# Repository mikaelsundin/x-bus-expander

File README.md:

# x-bus-expander
Emulated Model Train digital interface for getting upto 64-inputs and 64-outputs.

Setup the interface
======
* Solder everything.
* Connect up to four boards in a chain.
* Modify dip switches so every board have a unique combination.
* Connect USB-cable to PC and install CH340G driver.

How to connect Inputs
======
Switches can be connected to IN1 or IN2, pull-up is located on-board. 
The input signals must be electrical isolated from the rest of the system to not dammage anything.
If other devices that switches will be connected a optocoupler is suggested to electrical isolate the input.
C1-C8, C10-C17 is to avoid interface from inputs.

How to connect Outputs
======
Led:s / lamps can be connected to OUT1 and OUT2. The output voltage is equal to the VIN voltage.
With 2N7002 the maximum load current is 115mA and suggested voltage shall be 24V DC or less on VIN.
Remember to use correct polarity on VIN, marked with + and - on PCB.

How to use the interface
======
If you are running Freiwald TrainController (www.freiwald.com)
 choose "Lenz Digital Plus / LI100(F)" and correct com-port.
 The outputs will be named with Address 1-64
 The inputs will be named with Address 1-8 and Input 1-8

Hardware modification to Arduino nano:
======
UART signal CTS is attached to D9 (easiest done to clones with CH340G USB chip).
A jumper with 120R resistor to disable auto-reset feature is also added.

Hardware
======
The hardware is adapted to fit a single 10x5cm board.
Suggested manufacture is iteadstudio.com or elecrow.com
The PCB must be separated into two parts after manufacture.
Use a hacksaw for example if PCB tickness is 1.6mm. 
If running at 1.2mm the PCB can acually be cut by a ordinary scissors (the scissors will loose sharpness).

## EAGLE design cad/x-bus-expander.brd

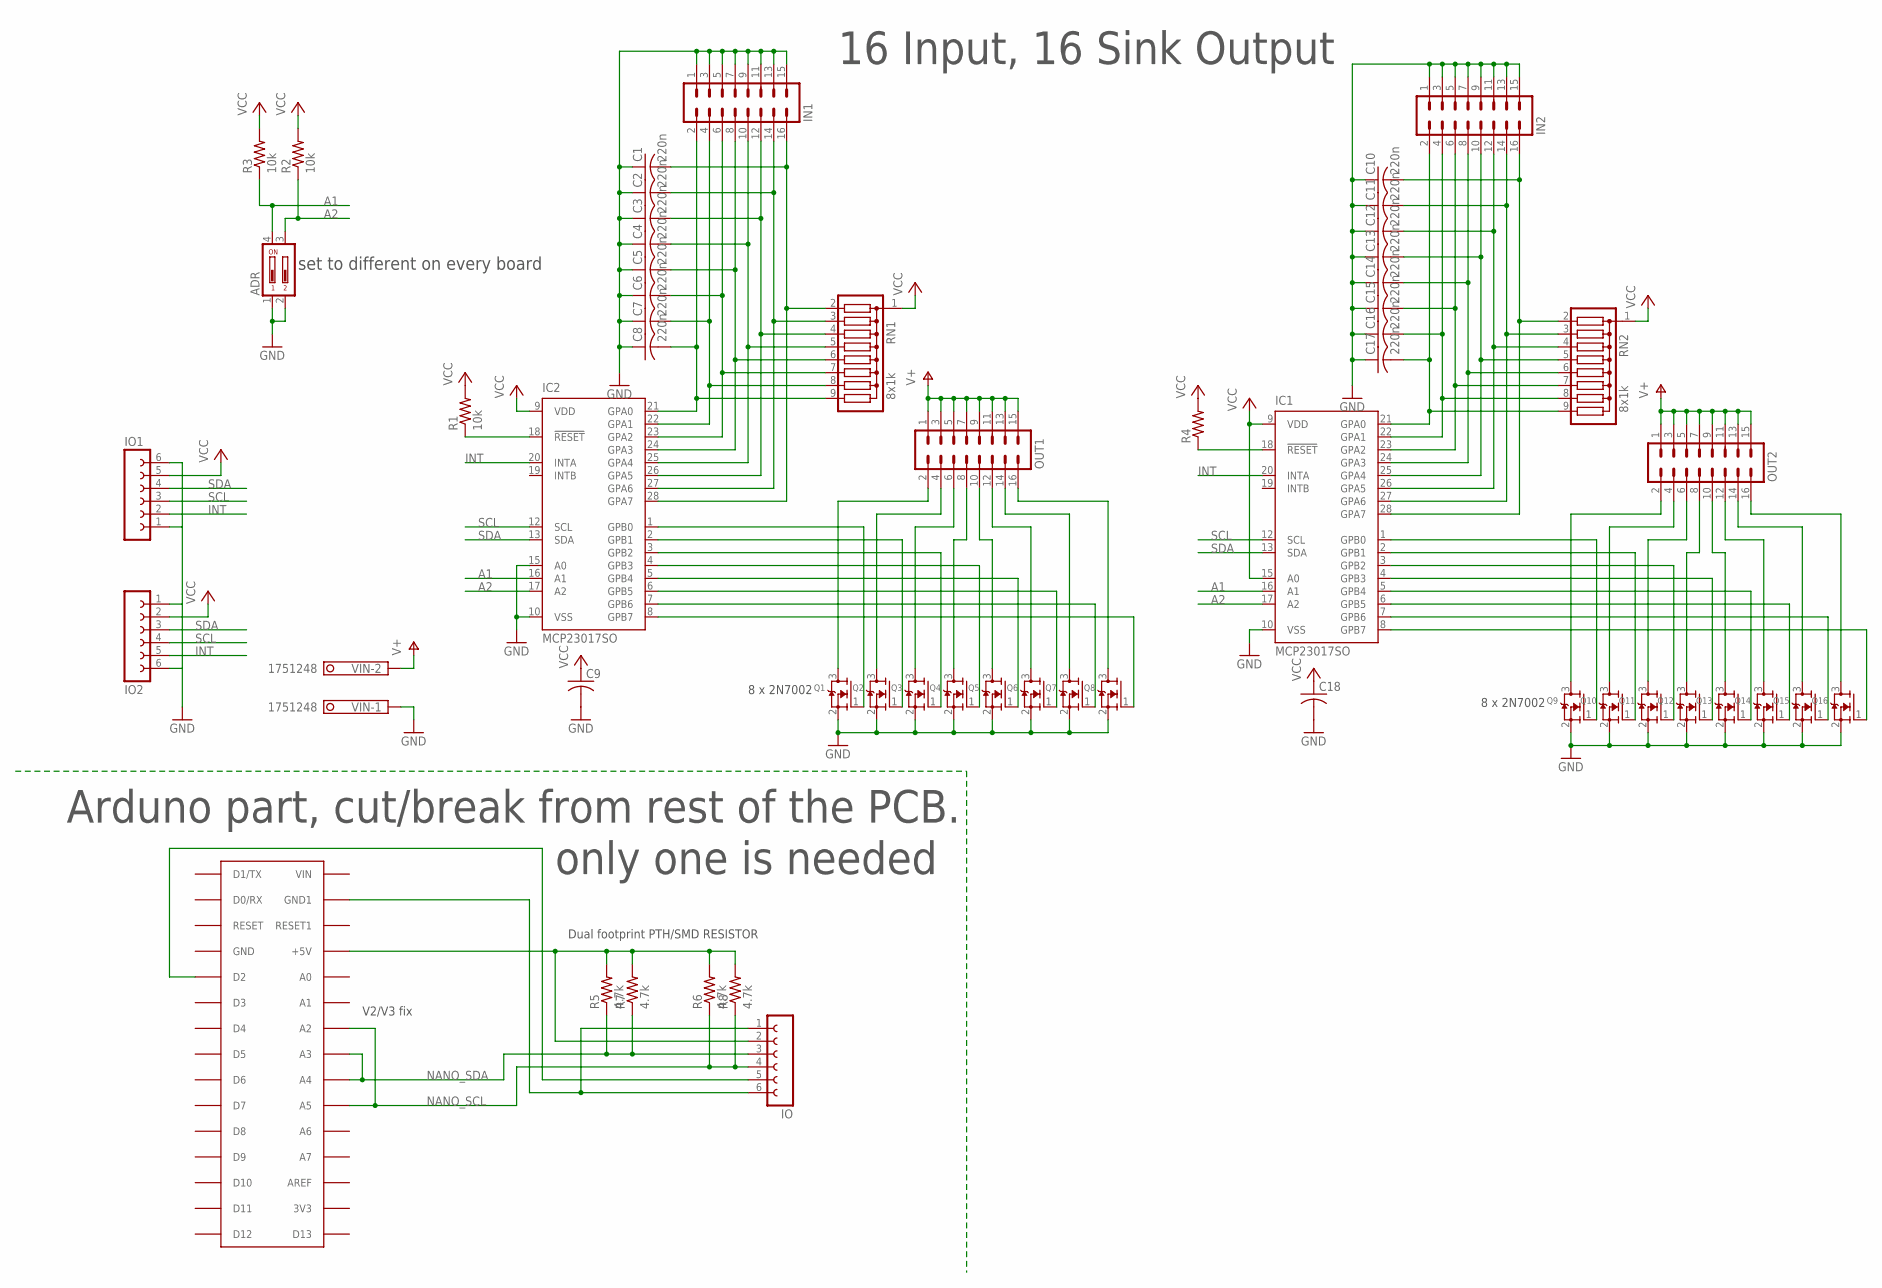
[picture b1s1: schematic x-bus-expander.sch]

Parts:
ADR: DIP02YL
C1, C2, C3, C4, C5, C6, C7, C8, C10, C11, C12, C13, C14, C15, C16, C17: 220n; C0805
C9, C18: C-USC0805; C0805
IC1, IC2: MCP23017SO; SO28W
IN1, IN2: ML16
IO, IO1, IO2: FE06W
OUT1, OUT2: ML16
Q1, Q2, Q3, Q4, Q5, Q6, Q7, Q8, Q9, Q10, Q11, Q12, Q13, Q14, Q15, Q16: MOSFET-NREFLOW; SOT23
R1, R2, R3: 10k; R0603
R4: R-US_R0603; R0603
R5, R6: 4.7k; 0309/10
R7, R8: 4.7k; R0603
RN1, RN2: 8x1k; SIL9
U$1: ARDUINONANO; PDIP-32
VIN: 1751248

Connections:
A1: ADR.4, IC1.16 (A1), IC2.16 (A1), R3.1
A2: ADR.3, IC1.17 (A2), IC2.17 (A2), R2.1
GND: ADR.1, ADR.2, C1.1, C2.1, C3.1, C4.1, C5.1, C6.1, C7.1, C8.1, C9.2, C10.1, C11.1, C12.1, C13.1, C14.1, C15.1, C16.1, C17.1, C18.2, IC1.10 (VSS), IC2.10 (VSS), IC2.15 (A0), IN1.1, IN1.3, IN1.5, IN1.7, IN1.9, IN1.11, IN1.13, IN1.15, IN2.1, IN2.3, IN2.5, IN2.7, IN2.9, IN2.11, IN2.13, IN2.15, IO1.1, IO1.6, IO2.1, IO2.6, Q1.2 (S), Q2.2 (S), Q3.2 (S), Q4.2 (S), Q5.2 (S), Q6.2 (S), Q7.2 (S), Q8.2 (S), Q9.2 (S), Q10.2 (S), Q11.2 (S), Q12.2 (S), Q13.2 (S), Q14.2 (S), Q15.2 (S), Q16.2 (S), VIN.1
INT: IC1.20 (INTA), IC2.20 (INTA), IO1.2, IO2.5
unnamed: OUT1.2, Q1.3 (D)
unnamed: OUT1.4, Q2.3 (D)
unnamed: OUT1.6, Q3.3 (D)
unnamed: OUT1.8, Q4.3 (D)
unnamed: OUT1.10, Q5.3 (D)
unnamed: OUT1.12, Q6.3 (D)
unnamed: OUT1.14, Q7.3 (D)
unnamed: OUT1.16, Q8.3 (D)
unnamed: IC2.1 (GPB0), Q1.1 (G)
unnamed: IC2.2 (GPB1), Q2.1 (G)
unnamed: IC2.3 (GPB2), Q3.1 (G)
unnamed: IC2.4 (GPB3), Q4.1 (G)
unnamed: IC2.5 (GPB4), Q5.1 (G)
unnamed: IC2.6 (GPB5), Q6.1 (G)
unnamed: IC2.7 (GPB6), Q7.1 (G)
unnamed: IC2.8 (GPB7), Q8.1 (G)
unnamed: C8.2, IC2.21 (GPA0), IN1.2, RN1.9
unnamed: C7.2, IC2.22 (GPA1), IN1.4, RN1.8
unnamed: C6.2, IC2.23 (GPA2), IN1.6, RN1.7
unnamed: C5.2, IC2.24 (GPA3), IN1.8, RN1.6
unnamed: C4.2, IC2.25 (GPA4), IN1.10, RN1.5
unnamed: C3.2, IC2.26 (GPA5), IN1.12, RN1.4
unnamed: C2.2, IC2.27 (GPA6), IN1.14, RN1.3
unnamed: C1.2, IC2.28 (GPA7), IN1.16, RN1.2
unnamed: IC2.18 (!RESET), R1.1
unnamed: OUT2.2, Q9.3 (D)
unnamed: OUT2.4, Q10.3 (D)
unnamed: OUT2.6, Q11.3 (D)
unnamed: OUT2.8, Q12.3 (D)
unnamed: OUT2.10, Q13.3 (D)
unnamed: OUT2.12, Q14.3 (D)
unnamed: OUT2.14, Q15.3 (D)
unnamed: OUT2.16, Q16.3 (D)
unnamed: IC1.1 (GPB0), Q9.1 (G)
unnamed: IC1.2 (GPB1), Q10.1 (G)
unnamed: IC1.3 (GPB2), Q11.1 (G)
unnamed: IC1.4 (GPB3), Q12.1 (G)
unnamed: IC1.5 (GPB4), Q13.1 (G)
unnamed: IC1.6 (GPB5), Q14.1 (G)
unnamed: IC1.7 (GPB6), Q15.1 (G)
unnamed: IC1.8 (GPB7), Q16.1 (G)
unnamed: C17.2, IC1.21 (GPA0), IN2.2, RN2.9
unnamed: C16.2, IC1.22 (GPA1), IN2.4, RN2.8
unnamed: C15.2, IC1.23 (GPA2), IN2.6, RN2.7
unnamed: C14.2, IC1.24 (GPA3), IN2.8, RN2.6
unnamed: C13.2, IC1.25 (GPA4), IN2.10, RN2.5
unnamed: C12.2, IC1.26 (GPA5), IN2.12, RN2.4
unnamed: C11.2, IC1.27 (GPA6), IN2.14, RN2.3
unnamed: C10.2, IC1.28 (GPA7), IN2.16, RN2.2
unnamed: IC1.18 (!RESET), R4.1
unnamed: IO.5, U$1.D2
unnamed: IO.1, IO.6, U$1.GND1
unnamed: IO.2, R5.2, R6.2, R7.2, R8.2, U$1.+5V
NANO_SCL: IO.4, R6.1, R8.1, U$1.A2, U$1.A5
NANO_SDA: IO.3, R5.1, R7.1, U$1.A3, U$1.A4
SCL: IC1.12 (SCL), IC2.12 (SCL), IO1.3, IO2.4
SDA: IC1.13 (SDA), IC2.13 (SDA), IO1.4, IO2.3
V+: OUT1.1, OUT1.3, OUT1.5, OUT1.7, OUT1.9, OUT1.11, OUT1.13, OUT1.15, OUT2.1, OUT2.3, OUT2.5, OUT2.7, OUT2.9, OUT2.11, OUT2.13, OUT2.15, VIN.2
VCC: C9.1, C18.1, IC1.9 (VDD), IC1.15 (A0), IC2.9 (VDD), IO1.5, IO2.2, R1.2, R2.2, R3.2, R4.2, RN1.1, RN2.1

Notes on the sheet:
Dual footprint PTH/SMD RESISTOR
8 x 2N7002
V2/V3 fix
16 Input, 16 Sink Output
Arduno part, cut/break from rest of the PCB.
only one is needed
set to different on every board

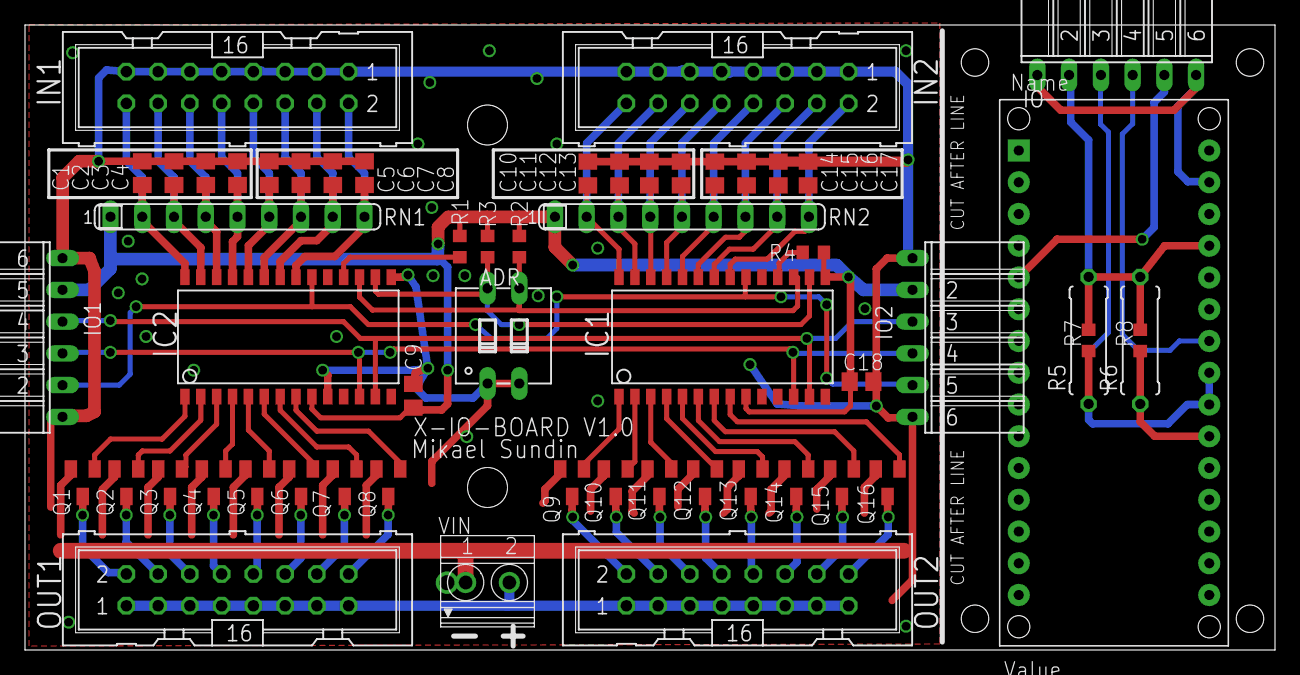
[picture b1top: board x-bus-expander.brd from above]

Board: 2 copper layers, 100.0 x 50.0 mm, 56 parts (0 on the bottom side), 63 nets.

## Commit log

2015-04-05 First upload, only test for now.
2015-04-05 Fixed a pcb bug when Arduion nano v2/v3 have different I2C pins placement.
2015-04-07 Added licence form to files.
2015-04-07 Removed extra chars from licence.md
2015-04-14 Added a MCP23017 driver and fixed connection between xbus and the MCP chips.
2015-07-18 fixed workaround for turnout command response, some program seems to need some data to continue to process..
2022-01-26 Updated schematic with some information and generated pdf for schematic.
